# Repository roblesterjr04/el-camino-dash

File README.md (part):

# El Camino Dash

A modular, open hardware and firmware digital instrument cluster, built on a CAN bus and plug-in cards.

The reference build is the dash of a **1964 Chevrolet El Camino**: three round touch screens sit where the original
gauges were, a main board behind them is shaped to that dash, and a small console works like the car's radio. But
only the main board knows which car it is in. Everything else (the screens, the sensor card, the audio card, the
radio, GPS, the LTE gateway, the console) is a node on one CAN bus that plugs into a **standard 2×15 card slot** or a
4-pin cable port. **Draw a main board for your own car, boat, kit car or bench, give it the same slots, and every card
in this repository plugs straight in.** Design a new card, and it adds its readings, alerts and settings pages to
the dash without a line of change to the screen firmware.

> **Status: work in progress.** The display, console and audio firmware run on bench hardware (Waveshare ESP32-P4
> round display boards, ESP32 dev kits). Nothing is installed in the car yet. Several cards exist as KiCad designs and
> as simulators in [`tools/`](tools/) but have not been built. Each README states what has and has not been tested
> on hardware. See [Status](#status).
>
> **Updated often; issues are not monitored, pull requests are welcome.** See [Contributing](#contributing).

## Contents

- [A modular platform](#a-modular-platform)
- [What it does](#what-it-does)
- [System overview](#system-overview-the-el-camino-reference-build)
- [Hardware](#hardware)
- [Firmware](#firmware)
- [Repository layout](#repository-layout)
- [Getting started](#getting-started)
- [Firmware updates without USB](#firmware-updates-without-usb)
- [Tests](#tests)
- [Making the boards](#making-the-boards)
- [Documentation map](#documentation-map)
- [Status](#status)
- [History](#history)
- [Contributing](#contributing)
- [Safety](#safety)
- [License](#license)

## A modular platform

```
          your main board                              the cards (unchanged, from any project)
  ┌───────────────────────────────┐
  │ shaped for your dash          │      ┌────────┐ ┌────────┐ ┌────────┐ ┌────────┐ ┌────────┐
  │ 1–3 screen headers            │◄─────┤ sensor │ │ audio  │ │ radio  │ │  GPS   │ │ yours  │
  │ 1–6 card slots (2×15)         │ slot │ card   │ │ card   │ │ card   │ │ card   │ │        │
  │ power, fuses, WAKE            │      └────────┘ └────────┘ └────────┘ └────────┘ └────────┘
  │ CAN bus, terminated at ends   │
  │ cable ports ──► console       │      every card: CAN + power on the slot, node number from the slot,
  └───────────────────────────────┘      services found by discovery, no configuration
```

The platform is three agreements, each documented in full:

| Agreement | What it fixes | Document |
| --- | --- | --- |
| **The card slot** | A 2×15, 2.54 mm socket: power (5 V, 3.3 V, switched and constant 12 V, AUX 12 V), CAN, a slot-ID resistor, WAKE, dash-light and reverse levels, an I2S digital audio rail and an analog audio bus. 80 × 60 mm cards standing on edge | [`docs/hardware/main_board_guide.md`](docs/hardware/main_board_guide.md) (designing a main board), [`docs/hardware/accessory_ports.md`](docs/hardware/accessory_ports.md) (the slot spec) |
| **The CAN bus** | Classic CAN, 500 kbit/s, terminated only on the main board; node numbers from the slot (`0x14 + slot − 1`); IDs as `channel base + node` | [`docs/protocols/can_guide.md`](docs/protocols/can_guide.md) (the guide), [`docs/protocols/can_bus.md`](docs/protocols/can_bus.md) |
| **The channel protocol** | How a card announces itself and uses the dash: alerts, sensor readings, menu pages, input, sounds, discovery | [`docs/protocols/can_channels.md`](docs/protocols/can_channels.md) |

What that buys you:

- **A main board is cheap to redraw.** It has no microcontroller: just power, the bus, the slots, the screen headers
  and the vehicle connectors. [`BenchBoard/`](BenchBoard/) (100 × 100 mm, two slots, one screen) is a complete
  small example; [`DigiDash2/`](DigiDash2/) is the full El Camino board.
- **Cards need no configuration.** A card reads its slot from a resistor on the main board and takes its node number
  from it. Two identical cards never clash; moving a card just renumbers it.
- **The dash finds services by discovery.** Cards announce what they produce and consume; the screens find the audio
  sink, the GPS or the internet gateway from those announcements.
- **New cards extend the dash without firmware changes elsewhere.** A card that publishes a SENSOR reading gets it
  logged and shown; one that defines an ALERT gets a chime and a banner; one that describes UI items gets a page in
  the menu on the round screens and on the console.
- **Fewer screens or slots is fine.** One screen runs as the center; slots can be any subset of the six.
- **The sensor card is a card too.** If your car's senders, speed sensor or tach differ, change the sensor card
  (or calibrate it from the menu), not the main board.

Ideas for cards nobody has built yet: transmission or oil temperature, wideband O2, tire pressure, parking sensors
(PLAY a tick sound on the audio card), steering-wheel buttons (INPUT), a data logger, a voice assistant on the I2S rail.
`tools/cards_sim.py` already simulates several of them, so the dash side can be tried before the hardware exists.

## What it does

- **Gauges.** Speed, odometer and trip, tach, fuel, oil pressure, coolant temperature, battery voltage, charge lamp,
  efficiency. Vector faces (LVGL) scale to 720×720 and 800×800 panels. If sensor data stops for 400 ms the needles
  fall to rest and the face shows **NO DATA** rather than a false zero.
- **Themes.** Classic (black glass, chrome, cream numerals), Modern (flat, orange arcs) and Fallout (green phosphor).
  A long press on the center screen changes all three screens at once.
- **Sensors on CAN.** The sensor card reads the original senders, the speed sensor, the tach signal, ignition, battery
  and the alternator lamp, keeps the odometer in FRAM, and sends the readings on CAN. Calibration is done from the
  menu ([`docs/protocols/sensor_calibration.md`](docs/protocols/sensor_calibration.md)).
- **Audio and phone.** The audio card is a Bluetooth A2DP / AVRCP / HFP sink with two stereo DACs (front and rear), a
  microphone input, a 10-band equaliser, fader and balance. Now playing, album art and the call card appear on the
  screens; calls are answered from the console or the touch screen.
- **Radio head unit.** The console (ESP32-S3, 256×64 OLED, two RetroSound-style knobs, IR receiver) selects the
  source, tunes the radio, handles calls and pairing, and shows every card's settings page.
- **Accessory protocol.** Cards announce themselves and publish alerts, sensors, menu pages, input and sounds through a
  documented CAN channel protocol ([`docs/protocols/can_channels.md`](docs/protocols/can_channels.md)), so a new card
  can add a page to the menu without changing the screen firmware.
- **More.** GPS time and location with a POSIX time zone, a reversing camera on the center screen (TVP5150 decoder),
  per-screen touch menus, settings kept in NVS and on SD. The cluster never uses Wi-Fi, apart from the console's
  firmware-update hotspot, which you open by hand while the car is parked.
- **Firmware updates without USB.** New firmware for the screens and the console goes in from a phone or a laptop
  with every board still in the dash: see [Firmware updates without USB](#firmware-updates-without-usb).

## System overview: the El Camino reference build

```
                         ┌──────────────── DigiDash main board (behind the screens) ────────────────┐
  vehicle 12 V ─────────►│ power, ignition / WAKE, reverse and dash-light sense, video decoder     │
  senders, speed, tach ─►│                                                                          │
  camera ───────────────►│  [J5] LEFT screen        [J1] CENTER screen        [J4] RIGHT screen     │
                         │  speedometer             tach / clock / media /    fuel / oil / temp /   │
                         │  ESP32-P4, node 0x02     efficiency, camera, GPS   charge                │
                         │                          ESP32-P4, node 0x01       ESP32-P4, node 0x03   │
                         │                                                                          │
                         │  six card slots (2×15): CAN, 5 V, 3.3 V, AUX 12 V, slot ID, I2S rail     │
                         │   ├ Sensor card   (node 0x04)   senders, speed, tach, odometer (FRAM)    │
                         │   ├ Audio card    (node 0x14+)  Bluetooth, DACs, mic, EQ; I2S clock master│
                         │   ├ Radio card                  Si4735 AM/FM with RDS                    │
                         │   ├ GPS card                    remote GPS puck                          │
                         │   └ LTE card                    SIMCom A7670 gateway                     │
                         │                                                                          │
                         │  cable ports ── ConsoleBoardRS (node 0x13): OLED, 2 knobs, IR            │
                         │  USB-CAN tap                                                             │
                         └──────────────────────────── CAN 500 kbit/s ──────────────────────────────┘
```

- **One CAN bus** (500 kbit/s, 11-bit IDs, terminated at the left and right screens) links everything. The cluster's
  own traffic (sensor frames, theme, settings, media, phone, console) is in
  [`docs/protocols/can_bus.md`](docs/protocols/can_bus.md); the accessory channel protocol that cards use is in
  [`docs/protocols/can_channels.md`](docs/protocols/can_channels.md).
- **The three screens run one firmware image.** Each reads its position from a strap on the main board's header
  (left to GND, right to 3.3 V, center open) and becomes the speedometer, the center screen or the right screen.
- **The center screen** owns the cluster settings, GPS time and location, the time zone, the camera and SD storage,
  and re-sends theme and settings to the others. Any screen can host the touch menu.
- **The sensor card is the source of truth** for readings and the odometer. A serial fallback (the original UART fan-out)
  can still feed the screens directly through a jumper.
- **The I2S rail** is a five-line digital audio bus to every slot. The audio card is its clock master; the radio and
  other cards ask for its return line before they send audio.

Pinouts, connectors and power are in [`docs/hardware/accessory_ports.md`](docs/hardware/accessory_ports.md) and
[`WIRING_PINOUT.md`](WIRING_PINOUT.md).

## Hardware

Every board is a KiCad 10 project generated by Python scripts in its `generate/` folder. The full list, with revision
history and status, is in [`HARDWARE.md`](HARDWARE.md).

| Board | What it is |
| --- | --- |
| [`DigiDash2/`](DigiDash2/) | Main board, rev 2: three screen headers, six card slots, power, video decoder, 4 layers, SMD assembled by the fab |
| [`DigiDash3/`](DigiDash3/) | Main board, rev 3: rev 2 with every part through-hole, 2 layers, for hand assembly |
| [`DigiDash/`](DigiDash/) | Main board, rev 1 (superseded): plug-in dev boards and accessory headers |
| [`SensorCard/`](SensorCard/) | Sensor card rev A: ATmega2560 + MCP2515 |
| [`SensorCard2/`](SensorCard2/) | Sensor card rev B: STM32G0B1 with built-in FDCAN, 2 layers |
| [`AudioCarrier/`](AudioCarrier/) | Audio card: ESP32-DevKitC-VE in sockets, 2× PCM5102A DAC, PCM1808 ADC + mic preamp, RCA outputs |
| [`RadioCard/`](RadioCard/) | AM/FM radio card: Si4735 tuner, STM32G0B1 |
| [`GPSCard/`](GPSCard/), [`GPSCard2/`](GPSCard2/) | GPS card: STM32G0B1 (rev A, SMD) or PIC18F26Q83 (rev B, through-hole) |
| [`LTECard/`](LTECard/) | LTE gateway card: ESP32-S3 + SIMCom A7670 core board |
| [`AICard/`](AICard/) | AI voice card: ESP32-S3 front end + a Pi-header Linux compute module (speech, local and online models). Not ordered; the module's fit is provisional |
| [`ConsoleBoardRS/`](ConsoleBoardRS/) | Console: ESP32-S3, SSD1322 OLED, RetroSound knobs on RJ9, IR receiver |
| [`ConsoleBoard/`](ConsoleBoard/) | Console, earlier variant with keys and encoders on the board |
| [`BenchBoard/`](BenchBoard/) | Bench stand-in for the main board: two slots, one screen, a USB-CAN header |
| [`Panel/`](Panel/) | All current boards on one fab panel |
| [`Housing/`](Housing/) | Onshape FeatureScript for the cluster housing; a turn-signal indicator puck |

Off-the-shelf parts: the screens are **Waveshare ESP32-P4-WIFI6-Touch-LCD-4C** (4", 720×720) on the left and right and
**-3.4C** (3.4", 800×800) in the center; they plug into the main board on 2×20 headers.

## Firmware

PlatformIO projects under [`firmware/`](firmware/). Shared code is in libraries; every board runs the firmware that
ships (there are no separate bench builds). Details, gestures, console commands and panel targets:
[`firmware/README.md`](firmware/README.md).

| Directory | Runs on | What |
| --- | --- | --- |
| [`firmware/esp32_p4_display`](firmware/esp32_p4_display/) | All three screens (ESP32-P4) | One image; position from the strap |
| [`firmware/esp32_p4_ui`](firmware/esp32_p4_ui/) | library | LVGL screen layer, gauge faces, menu, media / phone / accessory pages, touch |
| [`firmware/esp32_p4_common`](firmware/esp32_p4_common/) | library | Sensor link, panel setup, cluster I2C, watchdog, boot splash |
| [`firmware/elc_can`](firmware/elc_can/) | library | CAN IDs, frame codecs, TWAI driver with heartbeat and bus-off recovery |
| [`firmware/esp32s3_console`](firmware/esp32s3_console/) | Console (ESP32-S3) | Radio head unit UI on the OLED |
| [`firmware/esp32_classic_bt_audio`](firmware/esp32_classic_bt_audio/) | Audio card (classic ESP32) | Audio sink and Bluetooth bridge; builds [`arduino/sketches/esp32_audio_bridge`](arduino/sketches/) |
| [`firmware/sensor_card`](firmware/sensor_card/) | Sensor card rev A (ATmega2560) | Senders, speed, tach, odometer, calibration |
| [`firmware/sensor_card_stm32`](firmware/sensor_card_stm32/) | Sensor card rev B (STM32G0B1) | Port of rev A; same logic, new hardware layer |
| [`firmware/ai_card`](firmware/ai_card/) | AI voice card (ESP32-S3) | CAN node, rail audio, wake word, compute-module power, the assistant's allow-list |
| [`firmware/ai_agent`](firmware/ai_agent/) | AI card's compute module (Linux) | Speech to text, intents, on-board and online models, speech |
| [`firmware/esp32_p4_display_litmus`](firmware/esp32_p4_display_litmus/) | Any P4 panel | Panel bring-up test |
| [`arduino/sketches/`](arduino/sketches/) | various | Rev 1 sensor pack (ATmega328P), the audio bridge source, older experiments |

The radio, GPS, LTE and other cards do not have firmware yet; their behaviour on CAN is simulated by
[`tools/can_relay.py`](tools/can_relay.py) and the `*_sim.py` modules next to it.

## Repository layout

```
el-camino-dash/
├── README.md               this file
├── HARDWARE.md             every board: lineage, status, how to regenerate and order
├── WIRING_PINOUT.md        vehicle harness and screen header pinouts
├── firmware/               PlatformIO firmware and shared libraries
├── arduino/                Arduino sketches and arduino-cli helpers (rev 1 sensor pack, audio bridge source)
├── docs/
│   ├── protocols/          wire formats: CAN bus, CAN channels, sensor UART, USB link, calibration, I2C
│   └── hardware/           specs and plans: accessory ports, cards, housing envelope, harnesses, costing
├── tools/                  bench relay and card simulators, gauge / console previews, fab export scripts
├── scripts/                asset export (boot splash to RGB565)
├── assets/                 boot splash and the original Classic gauge art (design reference)
├── <Board>/                one directory per KiCad board (see Hardware)
└── Housing/                enclosure CAD
```

Each directory has its own README.

## Getting started

### Prerequisites

- **Python 3** for the tools and generators.
- **PlatformIO 6.1.18 or later.** Each `flash.sh` installs it into a local `.venv`; for a PlatformIO you installed
  yourself, add the builder's Python packages with `firmware/requirements-pio.txt` (see
  [`firmware/boards/README.md`](firmware/boards/README.md)). Platform and library versions are pinned in each `platformio.ini`.
- **A C++17 compiler** (Apple clang or gcc) for the host tests and the previews.
- **KiCad 10** to open or regenerate the boards.

### See the gauges without hardware

The faces render on a desktop with the same code that runs on the screens:

```bash
cd firmware/esp32_p4_display && pio run -e display-waveshare3c4 && cd -   # once, to fetch LVGL
tools/gauge_preview/build.sh
python3 tools/gauge_preview/preview.py faces.png 0,1,0 2,1,0 1,1,0
```

The console's OLED has the same kind of preview in [`tools/console_preview/`](tools/console_preview/). See
[`tools/README.md`](tools/README.md).

### Flash a screen

Any Waveshare ESP32-P4 round display board will do. Pick the environment that matches the panel
(`display-waveshare3c4` = 3.4" 800×800, `display-waveshare4c` = 4" 720×720); never flash one panel's profile on the
other.

```bash
cd firmware/esp32_p4_display
./flash.sh -e display-waveshare3c4 --upload-port /dev/cu.usbmodem…
```

Off the main board the position strap is open, so the board starts as the center screen. Type `role left`,
`role right` or `role auto` on its serial console (115200) to change that.

### Run a bench without a main board

[`tools/can_relay.py`](tools/can_relay.py) connects every board plugged into the computer over USB as if they were
on one CAN bus ([`docs/protocols/usb_link.md`](docs/protocols/usb_link.md)). It also sends a simulated drive in place
of the sensor card, the computer's clock in place of GPS, and simulated radio, audio, GPS, LTE and other cards:

```bash
python3 tools/can_relay.py            # every USB serial port found
python3 tools/can_relay.py --frames   # also log the frames
```

With a real CAN bus, plug a USB-CAN adapter into the main board's tap or the [`BenchBoard`](BenchBoard/).

### Other boards

```bash
firmware/esp32s3_console/flash.sh --upload-port /dev/cu.usbmodem…         # console
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
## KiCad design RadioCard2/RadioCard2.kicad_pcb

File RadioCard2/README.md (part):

# Radio card, rev B (through-hole)

The hand-assembled version of the [radio card](../RadioCard/README.md). Same job, same **80 × 60 mm slot card**, same
slot use (CAN, the I2S rail's BCK / WS in and RET out) and CAN IDs (`docs/hardware/radio_card.md`). The difference is
that **every part is through-hole**, so you can solder the whole board yourself, and the tuner is a plug-in module:

- the owner's **Si4737-C40-GU breakout** (FMBreakout.brd, OSH Park, 22.4 × 29.4 mm) in a **1×8 and a 1×9 socket**
  (J6 / J7), in place of rev A's Si4735-D60 (a DigiKey-only SSOP that had to be machine-placed). The Si4737 is AM / FM /
  weather band + RDS with digital audio out; it has no SW / LW, which this card never used
- a **PIC18F26Q83-I/SP** (SPDIP-28, in a socket), as [GPSCard2](../GPSCard2/README.md): PIC18 at 64 MHz with its own
  **CAN FD controller** (run as classic CAN at 500 kbit/s), I2C and 5 UARTs, with a 16 MHz HC-49 crystal (4x PLL)
- an **MCP2562-E/P** CAN transceiver (DIP-8; VDD 5 V, VIO 3.3 V, STBY low, no termination)
- a **74HC125** (DIP-14) as the RET buffer, off at reset, and an **MCP1700-3302E/TO** 3.3 V regulator (TO-92)
- the **edge-mount SMA** of rev A (Amphenol 132289, already on hand; the one part soldered by hand on both faces of the
  board edge) and the AM loopstick header J5 on the top edge
- **J3, a 6-pin Microchip ICSP header** and **J4** debug serial, both right angle on the left edge; two 3 mm LEDs
- axial 1/4 W resistors (10.16 mm pitch), radial capacitors (2.54 mm), an axial ferrite bead and an axial 56 nH inductor

**Antenna ESD: D2 is not fitted, D4 / D5 and SG1 stand in for it.** The TPD1E0B04 (0.13 pF) has no through-hole version,
and nothing through-hole comes close to AN383's ≤ 1 pF. In its place: **SG1**, a 0.25 mm PCB spark gap (bare copper, nothing
to fit) right under the SMA's centre pin, which takes the bulk of a big static hit, and **D4 / D5**, two 1N5711 Schottky
diodes back to back from the antenna node to ground, which clamp what gets past it to about ±0.4 V (the tuner input's
limit). The cost is about 4 pF on the antenna node: some FM signal, and L1 has to be tuned with them in (see
[Tuning L1](#tuning-l1)). If reception suffers, compare with them lifted. D2's 0402 pads stay on the board.

| Files | |
| --- | --- |
| `RadioCard2.kicad_sch` / `.kicad_pcb` / `.kicad_pro` | The card: 80 × 60 mm, 2 layers, every part on the parts side (F). KiCad 10 |
| `RadioCard2_BOM.csv` | Parts list (hand assembly) |
| `fab/` | Gerbers and drill files (`RadioCard2_gerbers.zip`) for a bare-board order. Nothing is machine-placed: the placement files list only J2, the edge-mount SMA, which you solder yourself |
| `generate/` | Scripts that produced the files: `gen_sch.py` new (rev A's circuit on GPSCard2's parts), `gen_pcb.py` from `GPSCard2/generate/` with rev A's RF keep-out. Stock KiCad symbols and footprints only |

## Signal paths

```
Slot BCK (15) ── R8 2k ── J6 pin 3  P3 = GPO3 / DCLK       (also the tuner's reference clock: RCLKSEL = DCLK)
Slot WS  (16) ── R7 2k ── J6 pin 2  DFS                    (C10 2.2 pF to GND on the WS side; R9 / R10 100k idle pull-downs)
J6 pin 1 DOUT ── R6 604 ── U5 74HC125 buffer A (OE = RA4, 10k up = off) ── R15 33 ── Slot RET (18)
Slot MCLK (24) ── R12 0 R (NOT FITTED) ── J7 pin 4 RCLK (R13 100k to GND)
SMA J2 ── SG1 gap to GND ── D4 / D5 1N5711 pair to GND ── L1 56 nH to GND ── C12 1 nF C0G ── J6 pin 6 FMI      J6 pin 7 RFG = GND
J5 (loopstick) ── C13 470 nF ── J6 pin 8 AMI                       JP2 (no shunt) joins the SMA node to the AM node
+3V3 ── FB1 ── +3V3A ── J7 pin 3 (3.3V, VA and VD on the breakout), C3 10 uF + C4 100 nF at the pin
PIC RC3 / RC4 (SCL1 / SDA1) ── J7 pins 6 / 5 SCLK / SDIO   (pull-ups: the breakout's own 10k to its 3.3 V)
PIC RA2 ── J7 pin 8 RST (R11 100k to GND)    PIC RB0 ── J6 pin 4 P2 = GPO2 / INT    JP1 ── J7 pin 7 SEN
Slot CANH / CANL (5 / 6) ── U2 MCP2562 ── TXD ◄ RB2 CANTX by PPS (pin 23),  RXD ── R5 1k ──► RB3 CANRX (pin 24)
Slot ID (11): R1 10k to 3.3 V here, the slot's resistor to GND on the main board ──► RA1 ANA1 (pin 3)
Slot +5 V (1 / 2) ── U3 MCP1700-3.3 ── +3V3 (PIC, MCP2562 VIO, 74HC125, FB1)
```

### The breakout's pins (J6 / J7)

As the breakout's own silk names them, each header counted from the **headphone-jack end** (socket pin 1). The breakout
sits **upside down** on the card: jack end toward the slot (silk "jack end"), so its FMI / AMI pins are nearest the SMA.

| Socket pin | J6 (breakout left header) | Si4737 pin | J7 (breakout right header) | Si4737 pin |
| --- | --- | --- | --- | --- |
| 1 | DOUT | 1 | LOUT (open) | 24 |
| 2 | DFS | 2 | ROUT (open) | 23 |
| 3 | P3 = GPO3 / DCLK | 3 | 3.3V (VA + VD) | 20, 21 |
| 4 | P2 = GPO2 / INT | 4 | RCLK | 19 |
| 5 | P1 = GPO1 (open: high or open at reset) | 5 | SDIO | 18 |
| 6 | FMI | 8 | SCLK | 17 |
| 7 | RFG (RF ground) | 9 | SEN | 16 |
| 8 | AMI | 12 | RST | 15 |
| 9 | | | GND | 13, 14 |

On the breakout itself: the DBYP capacitor (pin 22), 10k pull-ups on SDIO / SCLK and the headphone jack on LOUT / ROUT.
It has **no crystal** (the reference comes from DCLK), **no supply decoupling** (C3 / C4 here) and **no antenna coupling
capacitors** (C12 / C13 here).

### MCU pins (PIC18F26Q83, SPDIP-28)

| Pin | Port | Function | To |
| --- | --- | --- | --- |
| 1 | RE3 | MCLR / VPP | J3 pin 1, R2 10k to 3.3 V |
| 3 | RA1 | ANA1 | slot ID |
| 4 | RA2 | GPIO out | tuner RST (R11 100k to GND holds it in reset until the firmware runs) |
| 6 | RA4 | GPIO out | RET buffer OE, active low (R14 10k up = buffer off at reset and on a blank chip) |
| 8, 19 | VSS | GND | |
| 9 / 10 | RA7 / RA6 | OSC1 / OSC2 | Y1 16 MHz, C6 / C7 27 pF |
| 12 | RC1 | GPIO | LED D1 TUNED (high = on, R3 1k) |
| 13 | RC2 | GPIO | LED D3 STEREO / RDS (high = on, R4 1k) |
| 14 | RC3 | SCL1 | tuner SCLK |
| 15 | RC4 | SDA1 | tuner SDIO |
| 20 | VDD | 3.3 V | C5 100 nF |
| 21 | RB0 | INT0 | tuner GPO2 / INT |
| 23 | RB2 | CANTX (PPS) | MCP2562 TXD |
| 24 | RB3 | CANRX (POR default) | MCP2562 RXD (through R5 1k) |
| 25 | RB4 | U2TX (PPS) | J4 pin 2 |
| 26 | RB5 | U2RX (PPS) | J4 pin 3 |
| 27 | RB6 | ICSPCLK | J3 pin 5 |
| 28 | RB7 | ICSPDAT | J3 pin 4 |

All other pins are open: set them to outputs driven low, or analog, in firmware.

| Connector | Pins |
| --- | --- |
| J1, slot (2×15, right angle, bottom edge) | As rev A. Used: 1 / 2 +5 V, 3 / 4 / 7 / 19 / 20 GND, 5 CANH, 6 CANL, 11 slot ID, 15 BCK, 16 WS, 18 RET, 24 MCLK (only through R12, not fitted) |
| J2, antenna (SMA, edge mount, top edge) | Centre = FM antenna node, legs = GND (both faces) |
| J3, ICSP (1×6, right angle, left edge) | 1 MCLR/VPP, 2 VDD (3.3 V), 3 GND, 4 ICSPDAT, 5 ICSPCLK, 6 not used. Pin 1 is the lowest pin (PICkit / Snap pinout) |
| J4, debug serial (1×3, right angle, left edge) | 1 GND, 2 TX (out of the card), 3 RX (into the card); UART2, 3.3 V. Pin 1 is the lowest pin |
| J5, AM loopstick (1×2, right angle, top edge) | 1 AM node, 2 GND |
| J6 / J7, tuner breakout (1×8 / 1×9 female, 17.78 mm apart) | See the table above |
| JP1, tuner address (1×3 + shunt) | 1-2 = SEN low = I2C 0x11 (the firmware default); 2-3 = 0x63 |
| JP2, AM from whip (1×2, no shunt) | A shunt feeds the SMA to the AM input too (needs a car-whip AM network that AN383 does not give) |

## Board

- **Outline:** 80 × 60 mm, no mounting holes, the slot and the case hold it (as rev A).
- **J1** is placed exactly as on rev A and GPSCard2. **U1** lies along the board in the middle-left with Y1 under it,
  ICSP and debug on the left edge, as GPSCard2. **The breakout** sits at the top right (x 52-74, y 9-39) on its two
  sockets, jack end toward the slot: FMI / AMI at its top, near **J2** (SMA, x 70) and **J5** (x 58); DOUT / DFS / DCLK
  at its bottom, toward **U5** and the rail pins. **U2** sits above the slot's CAN pins, **U3** beside its 5 V pins.
- **RF keep-out:** no tracks on B in the top-right corner (x 60-80, y 0-23: the SMA, L1, the coupling caps and the
  breakout's RF pins), so the B ground pour is solid under the front end (as rev A).
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
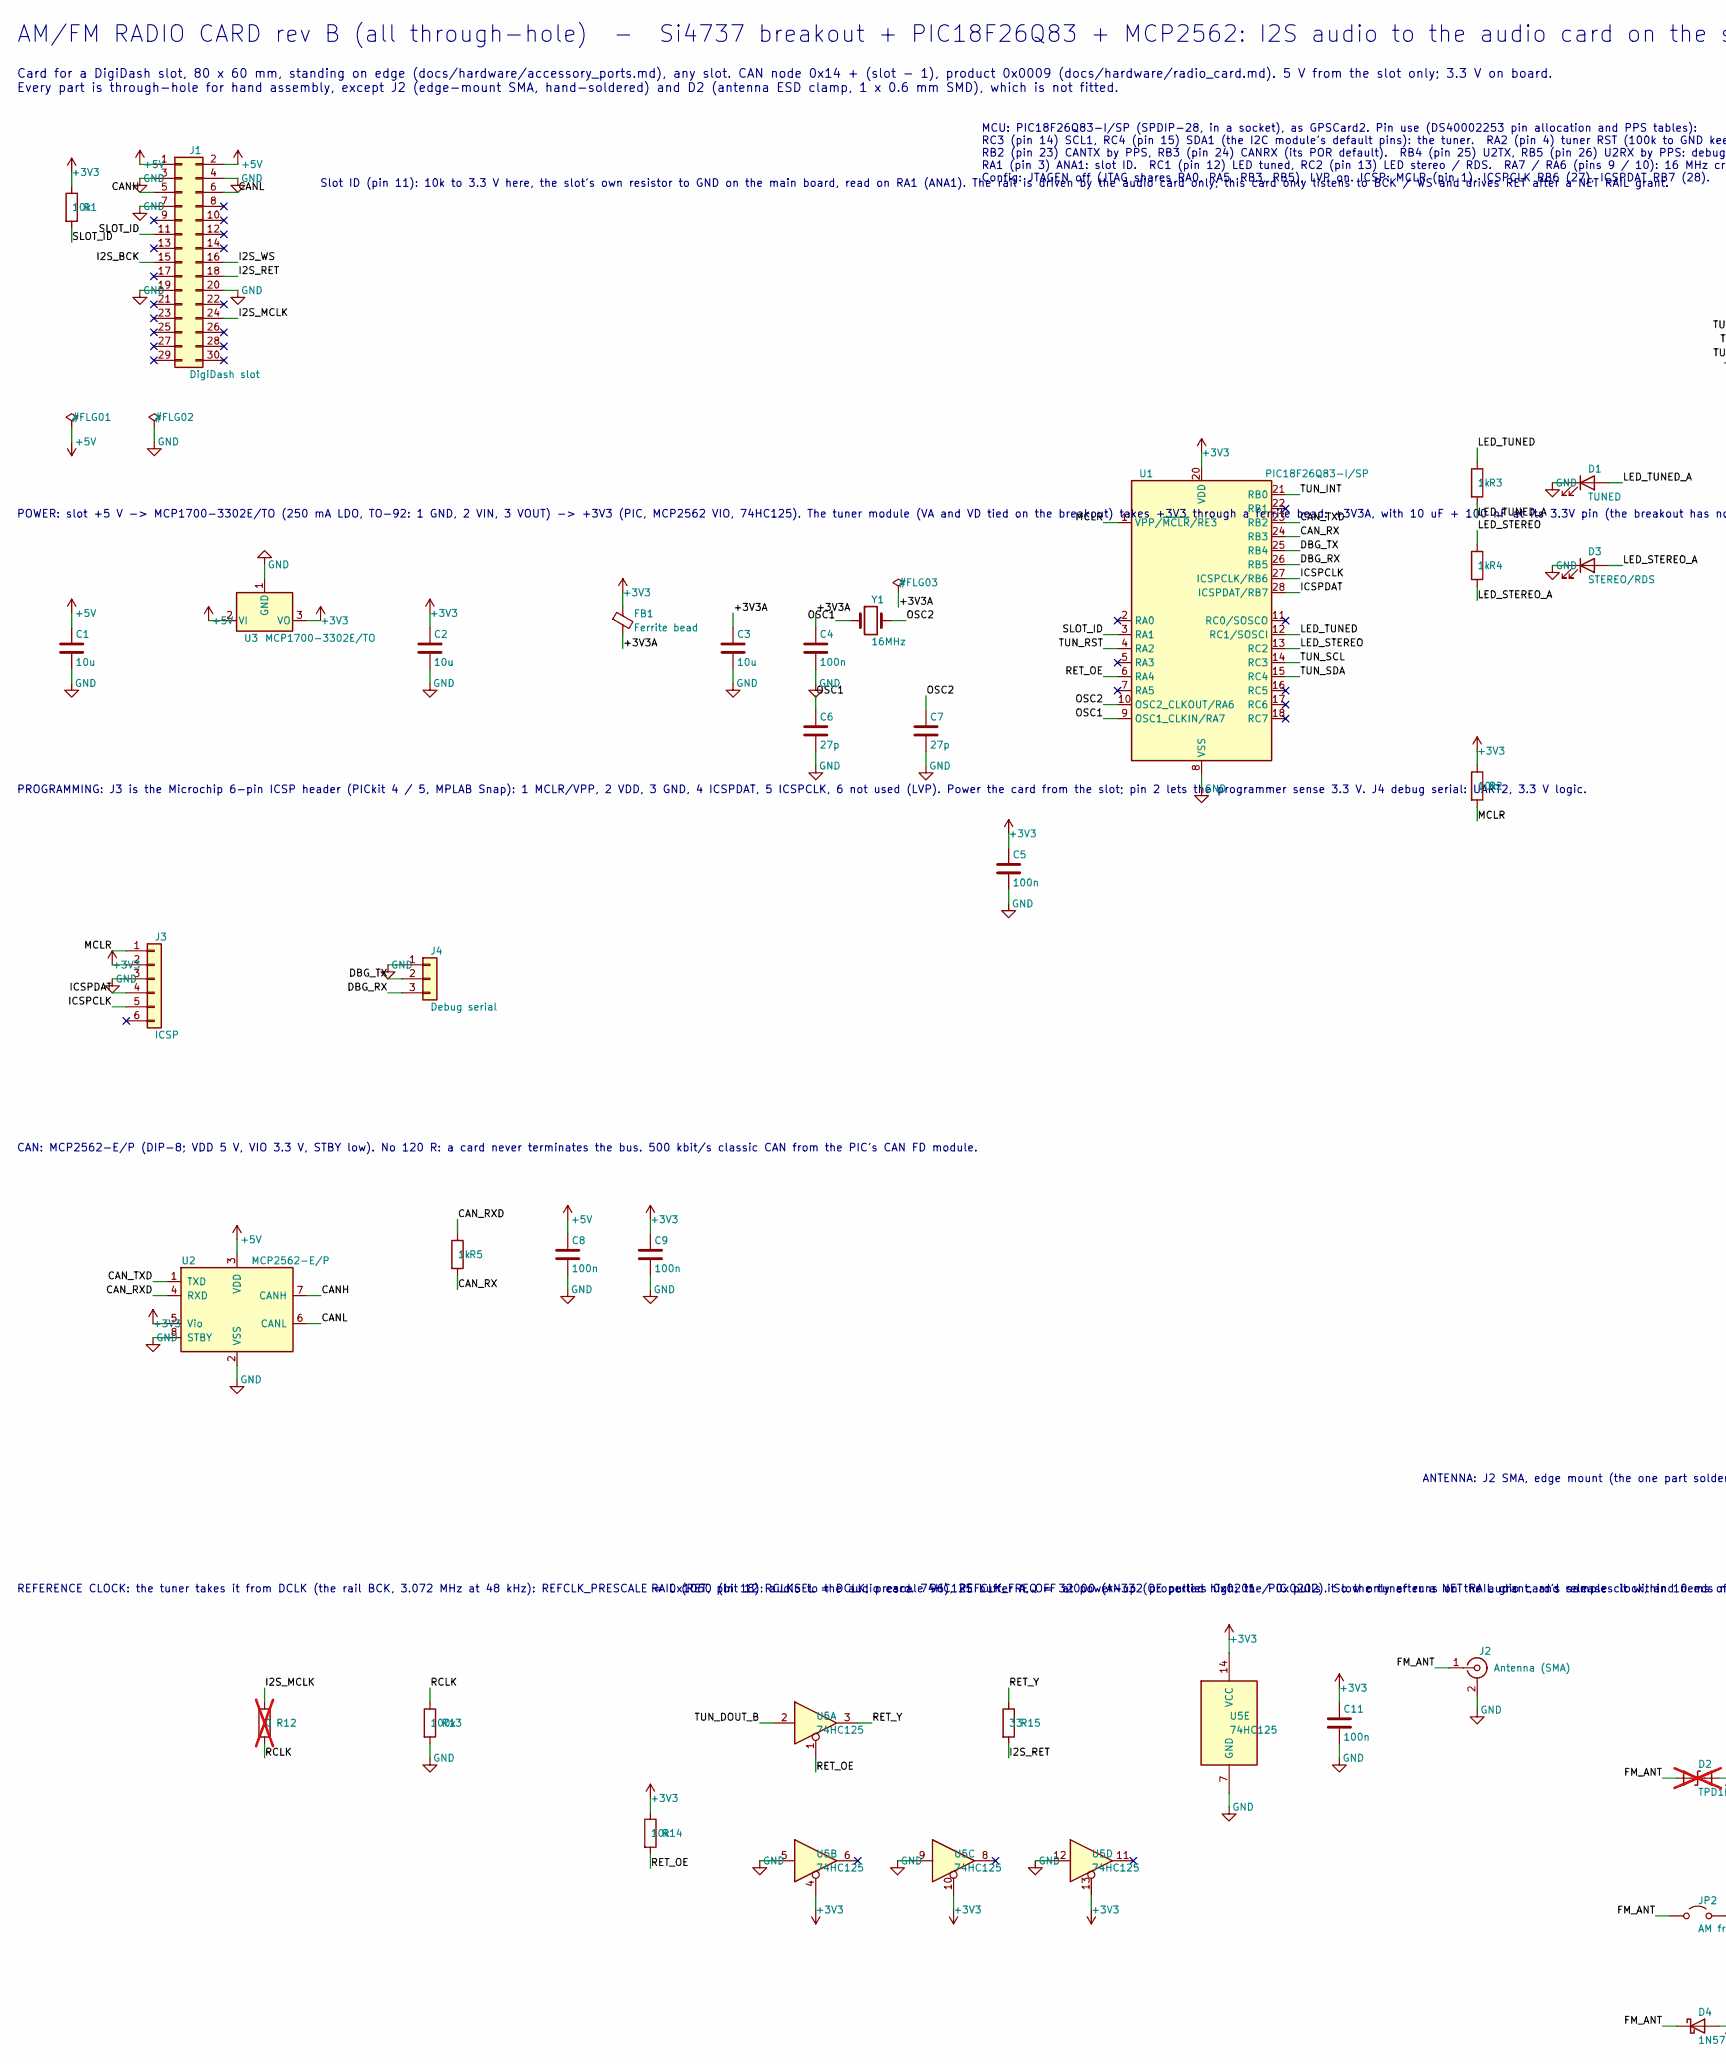
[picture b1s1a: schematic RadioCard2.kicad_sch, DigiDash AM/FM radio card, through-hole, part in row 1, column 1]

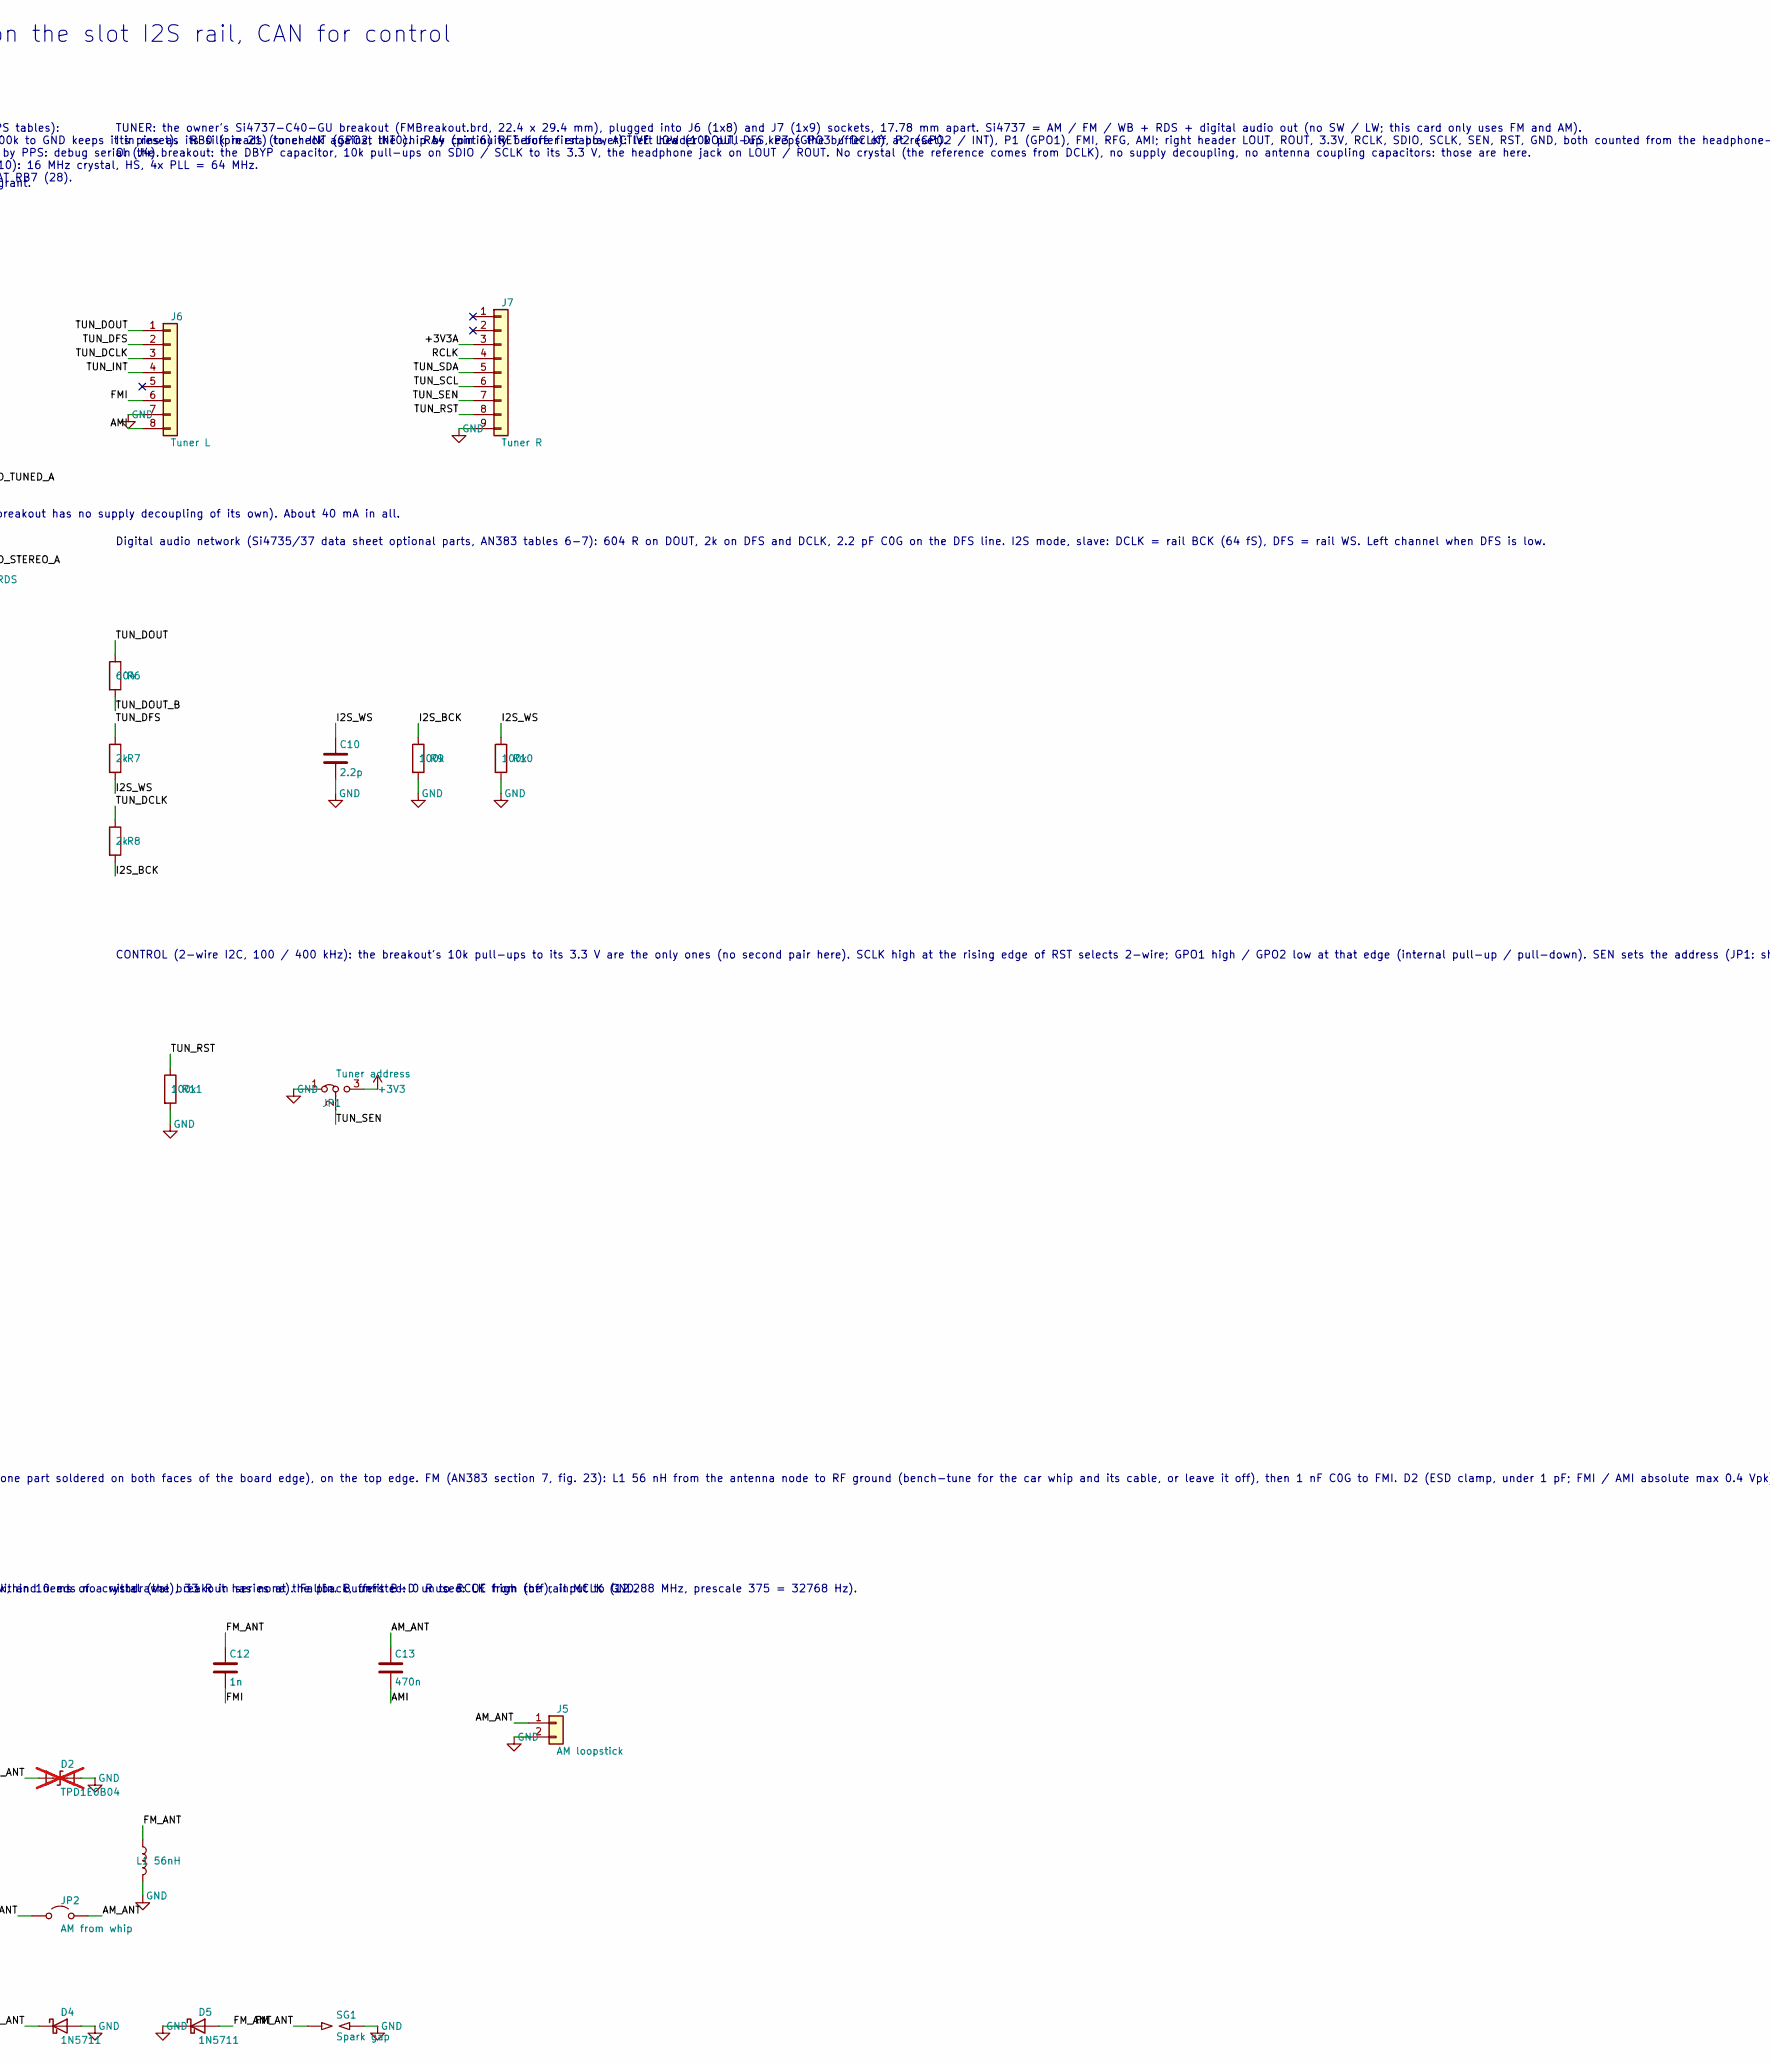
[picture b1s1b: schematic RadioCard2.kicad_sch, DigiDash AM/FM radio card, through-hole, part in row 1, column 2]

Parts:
C1, C2, C3: 10u; C_Disc_D5.0mm_W2.5mm_P2.50mm
C4, C5, C8, C9, C11: 100n; C_Disc_D5.0mm_W2.5mm_P2.50mm
C6, C7: 27p; C_Disc_D5.0mm_W2.5mm_P2.50mm
C10: 2.2p; C_Disc_D5.0mm_W2.5mm_P2.50mm
C12: 1n; C_Disc_D5.0mm_W2.5mm_P2.50mm
C13: 470n; C_Disc_D5.0mm_W2.5mm_P2.50mm
D1: TUNED; LED_D3.0mm
D2: TPD1E0B04; D_0402_1005Metric; not fitted
D3: STEREO/RDS; LED_D3.0mm
D4, D5: 1N5711; D_DO-35_SOD27_P2.54mm_Vertical_CathodeUp
FB1: Ferrite bead; L_Axial_L5.0mm_D3.6mm_P10.00mm_Horizontal_Murata_BL01RN1A2A2
J1: DigiDash slot; PinHeader_2x15_P2.54mm_Horizontal
J2: Antenna (SMA); SMA_Amphenol_132289_EdgeMount
J3: ICSP; PinHeader_1x06_P2.54mm_Horizontal
J4: Debug serial; PinHeader_1x03_P2.54mm_Horizontal
J5: AM loopstick; PinHeader_1x02_P2.54mm_Horizontal
J6: Tuner L; PinSocket_1x08_P2.54mm_Vertical
J7: Tuner R; PinSocket_1x09_P2.54mm_Vertical
JP1: Tuner address; PinHeader_1x03_P2.54mm_Vertical
JP2: AM from whip; PinHeader_1x02_P2.54mm_Vertical
L1: 56nH; L_Axial_L5.3mm_D2.2mm_P7.62mm_Horizontal_Vishay_IM-1
R1, R2, R14: 10k; R_Axial_DIN0207_L6.3mm_D2.5mm_P10.16mm_Horizontal
R3, R4, R5: 1k; R_Axial_DIN0207_L6.3mm_D2.5mm_P10.16mm_Horizontal
R6: 604; R_Axial_DIN0207_L6.3mm_D2.5mm_P10.16mm_Horizontal
R7, R8: 2k; R_Axial_DIN0207_L6.3mm_D2.5mm_P10.16mm_Horizontal
R9, R10, R11, R13: 100k; R_Axial_DIN0207_L6.3mm_D2.5mm_P10.16mm_Horizontal
R12: 0; R_Axial_DIN0207_L6.3mm_D2.5mm_P10.16mm_Horizontal; not fitted
R15: 33; R_Axial_DIN0207_L6.3mm_D2.5mm_P10.16mm_Horizontal
SG1: Spark gap; SparkGap_0.25mm
U1: PIC18F26Q83-I/SP; DIP-28_W7.62mm_Socket
U2: MCP2562-E/P; DIP-8_W7.62mm
U3: MCP1700-3302E/TO; TO-92_Inline_Wide
U5: 74HC125; DIP-14_W7.62mm
Y1: 16MHz; Crystal_HC49-4H_Vertical

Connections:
+3V3: C2.1, C5.1, C9.1, C11.1, FB1.1, J3.2, JP1.3 (B), R1.1, R2.1, R14.1, U1.20 (VDD), U2.5 (Vio), U3.3 (VO), U5.4, U5.10, U5.13, U5.14 (VCC)
+5V: C1.1, C8.1, J1.1, J1.2, U2.3 (VDD), U3.2 (VI)
/+3V3A: C3.1, C4.1, FB1.2, J7.3
/AMI: C13.2, J6.8
/AM_ANT: C13.1, J5.1, JP2.2 (B)
/CANH: J1.5, U2.7 (CANH)
/CANL: J1.6, U2.6 (CANL)
/CAN_RX: R5.2, U1.24 (RB3)
/CAN_RXD: R5.1, U2.4 (RXD)
/CAN_TXD: U1.23 (RB2), U2.1 (TXD)
/DBG_RX: J4.3, U1.26 (RB5)
/DBG_TX: J4.2, U1.25 (RB4)
/FMI: C12.2, J6.6
/FM_ANT: C12.1, D2.1 (A1), D4.1 (K), D5.2 (A), J2.1 (In), JP2.1 (A), L1.1, SG1.1
/I2S_BCK: J1.15, R8.2, R9.1
/I2S_MCLK: J1.24, R12.1
/I2S_RET: J1.18, R15.2
/I2S_WS: C10.1, J1.16, R7.2, R10.1
/ICSPCLK: J3.5, U1.27 (ICSPCLK/RB6)
/ICSPDAT: J3.4, U1.28 (ICSPDAT/RB7)
/LED_STEREO: R4.1, U1.13 (RC2)
/LED_STEREO_A: D3.2 (A), R4.2
/LED_TUNED: R3.1, U1.12 (RC1/SOSCI)
/LED_TUNED_A: D1.2 (A), R3.2
/MCLR: J3.1, R2.2, U1.1 (VPP/~MCLR/RE3)
/OSC1: C6.1, U1.9 (OSC1_CLKIN/RA7), Y1.1
/OSC2: C7.1, U1.10 (OSC2_CLKOUT/RA6), Y1.2
/RCLK: J7.4, R12.2, R13.1
/RET_OE: R14.2, U1.6 (RA4), U5.1
/RET_Y: R15.1, U5.3
/SLOT_ID: J1.11, R1.2, U1.3 (RA1)
/TUN_DCLK: J6.3, R8.1
/TUN_DFS: J6.2, R7.1
/TUN_DOUT: J6.1, R6.1
/TUN_DOUT_B: R6.2, U5.2
/TUN_INT: J6.4, U1.21 (RB0)
/TUN_RST: J7.8, R11.1, U1.4 (RA2)
/TUN_SCL: J7.6, U1.14 (RC3)
/TUN_SDA: J7.5, U1.15 (RC4)
/TUN_SEN: J7.7, JP1.2 (C)
GND: C1.2, C2.2, C3.2, C4.2, C5.2, C6.2, C7.2, C8.2, C9.2, C10.2, C11.2, D1.1 (K), D2.2 (A2), D3.1 (K), D4.2 (A), D5.1 (K), J1.3, J1.4, J1.7, J1.19, J1.20, J2.2 (Ext), J3.3, J4.1, J5.2, J6.7, J7.9, JP1.1 (A), L1.2, R9.2, R10.2, R11.2, R13.2, SG1.2, U1.8 (VSS), U1.19 (VSS), U2.2 (VSS), U2.8 (STBY), U3.1 (GND), U5.5, U5.7 (GND), U5.9, U5.12

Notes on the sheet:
AM/FM RADIO CARD rev B (all through-hole) - Si4737 breakout + PIC18F26Q83 + MCP2562: I2S audio to the audio card on the slot I2S rail, CAN for control
Card for a DigiDash slot, 80 x 60 mm, standing on edge (docs/hardware/accessory_ports.md), any slot. CAN node 0x14 + (slot - 1), product 0x0009 (docs/hardware/radio_card.md). 5 V from the slot only; 3.3 V on board. Every part is through-hole for hand assembly, except J2 (edge-mount SMA, hand-solder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
Slot ID (pin 11): 10k to 3.3 V here, the slot's own resistor to GND on the main board, read on RA1 (ANA1). The rail is driven by the audio card only; this card only listens to BCK / WS and drives RET after a NET RAIL grant.
POWER: slot +5 V -> MCP1700-3302E/TO (250 mA LDO, TO-92: 1 GND, 2 VIN, 3 VOUT) -> +3V3 (PIC, MCP2562 VIO, 74HC125). The tuner module (VA and VD tied on the breakout) takes +3V3 through a ferrite bead: +3V3A, with 10 uF + 100 nF at its 3.3V pin (the breakout has no supply decoupling of its own). Abo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
MCU: PIC18F26Q83-I/SP (SPDIP-28, in a socket), as GPSCard2. Pin use (DS40002253 pin allocation and PPS tables): RC3 (pin 14) SCL1, RC4 (pin 15) SDA1 (the I2C module's default pins): the tuner. RA2 (pin 4) tuner RST (100k to GND keeps it in reset). RB0 (pin 21) tuner INT (GPO2, INT0). RA4 (pin 6) RE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
PROGRAMMING: J3 is the Microchip 6-pin ICSP header (PICkit 4 / 5, MPLAB Snap): 1 MCLR/VPP, 2 VDD, 3 GND, 4 ICSPDAT, 5 ICSPCLK, 6 not used (LVP). Power the card from the slot; pin 2 lets the programmer sense 3.3 V. J4 debug serial: UART2, 3.3 V logic.
CAN: MCP2562-E/P (DIP-8; VDD 5 V, VIO 3.3 V, STBY low). No 120 R: a card never terminates the bus. 500 kbit/s classic CAN from the PIC's CAN FD module.
TUNER: the owner's Si4737-C40-GU breakout (FMBreakout.brd, 22.4 x 29.4 mm), plugged into J6 (1x8) and J7 (1x9) sockets, 17.78 mm apart. Si4737 = AM / FM / WB + RDS + digital audio out (no SW / LW; this card only uses FM and AM). Its pins as its silk reads (to check against the chip by continuity be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
Digital audio network (Si4735/37 data sheet optional parts, AN383 tables 6-7): 604 R on DOUT, 2k on DFS and DCLK, 2.2 pF C0G on the DFS line. I2S mode, slave: DCLK = rail BCK (64 fS), DFS = rail WS. Left channel when DFS is low.
CONTROL (2-wire I2C, 100 / 400 kHz): the breakout's 10k pull-ups to its 3.3 V are the only ones (no second pair here). SCLK high at the rising edge of RST selects 2-wire; GPO1 high / GPO2 low at that edge (internal pull-up / pull-down). SEN sets the address (JP1: shunt 1-2 = SEN low = 0x11; 2-3 = 0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
REFERENCE CLOCK: the tuner takes it from DCLK (the rail BCK, 3.072 MHz at 48 kHz): REFCLK_PRESCALE = 0x1060 (bit 12 RCLKSEL = DCLK, prescale 96), REFCLK_FREQ = 32000 (AN332 properties 0x0201 / 0x0202). So the tuner runs on the audio card's sample clock, and needs no crystal (the breakout has none).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
RAIL (RET, pin 18): audio to the audio card. 74HC125 buffer A, OFF at power-up (OE pulled high; the PIC pulls it low only after a NET RAIL grant, and releases it within 10 ms of a withdrawal), 33 R in series at the pin. Buffers B-D unused: OE high (off), input to GND.
ANTENNA: J2 SMA, edge mount (the one part soldered on both faces of the board edge), on the top edge. FM (AN383 section 7, fig. 23): L1 56 nH from the antenna node to RF ground (bench-tune for the car whip and its cable, or leave it off), then 1 nF C0G to FMI. D2 (ESD clamp, under 1 pF; FMI / AMI a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

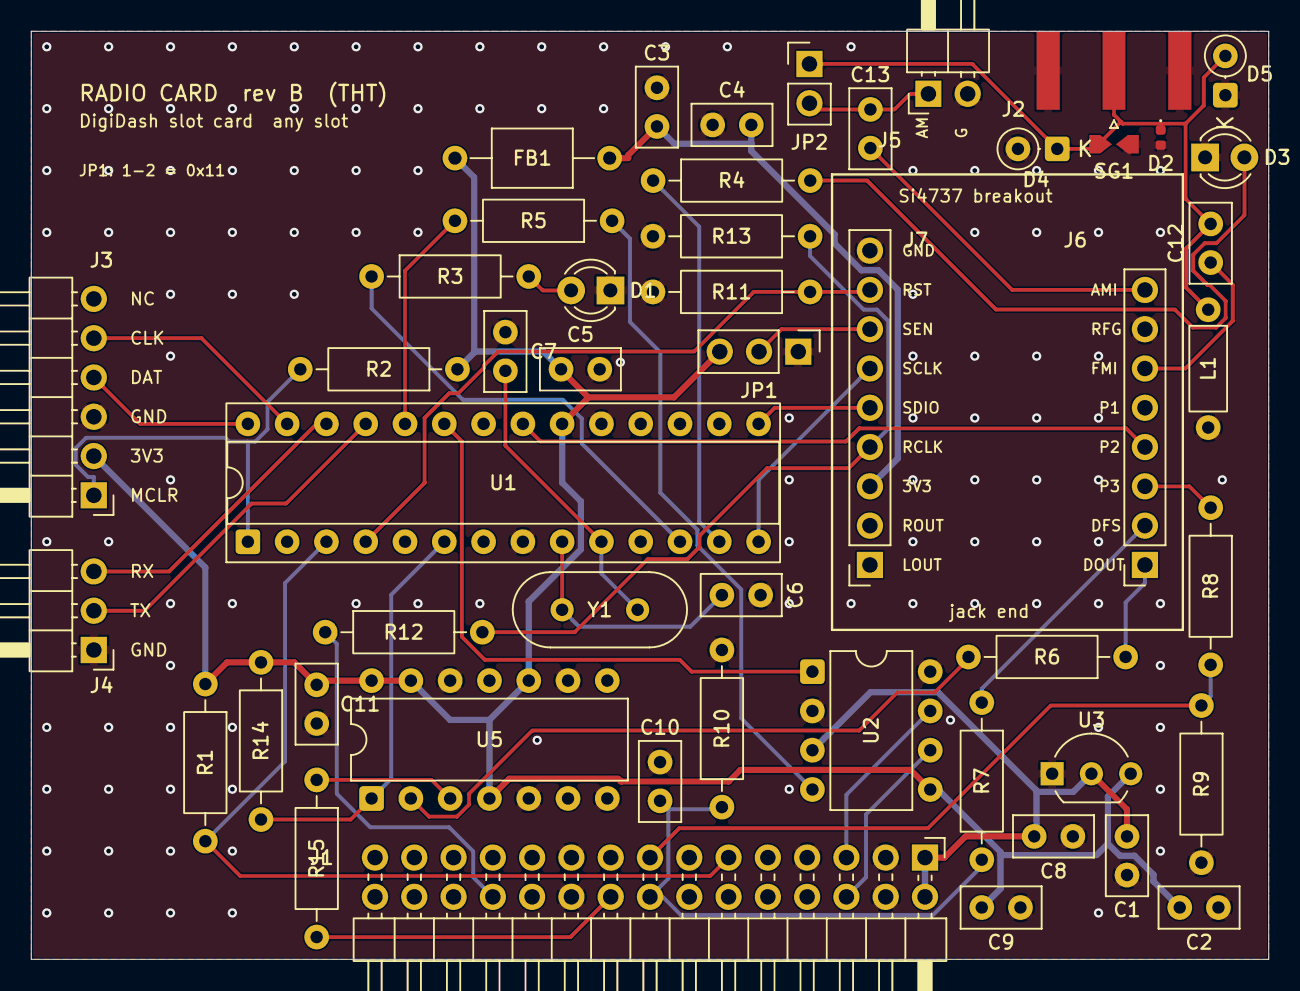
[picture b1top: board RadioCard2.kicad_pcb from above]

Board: 2 copper layers, 80.0 x 60.0 mm, 50 parts (0 on the bottom side), 41 nets.

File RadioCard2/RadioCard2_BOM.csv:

Qty,Designators,Manufacturer part,Description,Package,Type,Side,Notes
1,U1,Microchip PIC18F26Q83-I/SP,"MCU: PIC18, 64 MHz, 64 KB flash, 4 KB RAM, CAN FD, I2C, 5 UARTs, 1.8-5.5 V",SPDIP-28 (0.3 in),THT,Top,"Fit in a socket (next line). Notch / pin 1 toward J3 (left). Arrives blank: programmed over J3 (ICSP)"
1,U1 socket,"Any 28-pin 0.3 in (narrow) DIP socket","IC socket for U1",DIP-28 0.3 in,THT,Top,"Turned-pin or leaf type. Solder the socket, not the PIC"
1,U2,Microchip MCP2562-E/P,"CAN FD transceiver, VDD 5 V, VIO 3.3 V",PDIP-8,THT,Top,"An 8-pin 0.3 in socket fits too"
1,U3,Microchip MCP1700-3302E/TO,"LDO 3.3 V 250 mA (1 GND, 2 VIN, 3 VOUT)",TO-92,THT,Top,"Wide-spaced pads (2.54 mm): bend the outer legs out. Flat face as the silk shows"
1,U5,Texas Instruments SN74HC125N,"74HC125: quad 3-state buffer, OE active low (buffer A drives the rail's RET pin)",PDIP-14,THT,Top,"Runs at 3.3 V. Any 74HC125 / 74AHC125 in DIP-14. A 14-pin socket fits too"
1,Tuner,"Si4737-C40-GU breakout (FMBreakout.brd, OSH Park, owner-built)","AM / FM / WB + RDS tuner with digital audio out, on a 22.4 x 29.4 mm board with a 1 x 8 and a 1 x 9 male header",Module,Module,Top,"Already built. Plugs into J6 / J7, headphone jack toward the slot (silk 'jack end'). Check its header pinout against the chip by continuity before first power"
1,Y1,Abracon ABL-16.000MHZ-B2,"Crystal 16 MHz, 18 pF load",HC-49/US,THT,Top,"Any 16 MHz HC-49/US crystal with an 18 pF load"
2,C6 C7,"Any, C0G / NP0, 50 V","27p: Capacitor 27 pF C0G (crystal load)","Radial, 2.54 mm lead spacing",THT,Top,
5,C4 C5 C8 C9 C11,KEMET C320C104K5R5TA,"100n: Capacitor 100 nF X7R 50 V","Radial, 2.54 mm lead spacing",THT,Top,"C4 = tuner 3.3V (at J7 pin 3), C5 = U1 VDD (pin 20), C8 = MCP2562 VDD, C9 = MCP2562 VIO, C11 = 74HC125 VCC"
3,C1 C2 C3,"Any, X5R, 10 V or more","10u: Capacitor 10 uF ceramic (C1 slot 5 V / U3 in, C2 U3 out, C3 tuner supply)","Radial MLCC, 2.54 mm lead spacing",THT,Top,"Ceramic, not electrolytic: the MCP1700 wants ceramic in and out"
1,C12,"Any, C0G / NP0, 50 V","1n: Capacitor 1 nF C0G (FM coupling to FMI)","Radial, 2.54 mm lead spacing",THT,Top,"C0G only"
1,C13,"Any, X7R, 16 V or more","470n: Capacitor 470 nF (AM coupling to AMI)","Radial MLCC, 2.54 mm lead spacing",THT,Top,
1,C10,"Any, C0G / NP0, 50 V","2.2p: Capacitor 2.2 pF C0G (noise capacitor on the DFS line)","Radial, 2.54 mm lead spacing",THT,Top,"C0G, +-0.25 pF if you can get it"
1,FB1,Murata BL01RN1A2A2B,"Ferrite bead, through-hole (tuner supply)",Axial bead,THT,Top,"Any through-hole bead of about 100 R at 100 MHz, rated 0.1 A or more"
1,L1,"56 nH axial RF inductor","56nH: FM antenna match to RF ground (AN383 fig. 23), Q >= 15 at 100 MHz","Axial, 7.62 mm lead spacing",THT,Top,"Or wind about 5 turns of 0.5 mm enamelled wire on a 3 mm form. Tuned on the bench (README, Tuning L1): fit it in two turned-pin socket contacts so values swap without desoldering. Always fit one: it also drains static off the whip"
2,L1 socket,"2 contacts cut from a turned-pin (machined) SIP socket strip","Sockets for L1, so it can be swapped while tuning",-,THT,Top,"Optional. Any machined-pin strip whose tails fit 0.8 mm holes"
3,R1 R2 R14,"Any 1/4 W 1 % metal film (Yageo MFR-25FBF52-10K or equal)","10k: Resistor (R1 slot ID pull-up, R2 MCLR pull-up, R14 RET buffer off at reset)",Axial DIN0207,THT,Top,
3,R3 R4 R5,"Any 1/4 W 1 % metal film","1k: Resistor (R3 / R4 LEDs, R5 CAN RXD series)",Axial DIN0207,THT,Top,
1,R6,"Any 1/4 W 1 % metal film","604: Resistor (DOUT series)",Axial DIN0207,THT,Top,"600-620 R is fine"
2,R7 R8,"Any 1/4 W 1 % metal film","2k: Resistor (DFS / DCLK series)",Axial DIN0207,THT,Top,
4,R9 R10 R11 R13,"Any 1/4 W 1 % metal film","100k: Resistor (R9 / R10 rail BCK / WS idle pull-downs, R11 tuner reset, R13 RCLK)",Axial DIN0207,THT,Top,
1,R15,"Any 1/4 W 1 % metal film","33: Resistor (RET series, at the rail pin)",Axial DIN0207,THT,Top,
0,R12,"Any 0 R link","0: MCLK to RCLK link (fallback reference clock)",Axial DIN0207,THT,Top,DNP
0,D2,Texas Instruments TPD1E0B04DPYR,"ESD clamp, 1 channel, 0.13 pF (antenna)",X1SON-2 1.0 x 0.6 mm,SMD,Top,"DNP: no through-hole version exists; D4 / D5 and SG1 stand in for it. Pads are on the board if it is ever fab-placed"
2,D4 D5,Vishay 1N5711,"Schottky diode 70 V, 2 pF: antenna ESD clamp pair, back to back to GND (about 0.4 V clamp)",DO-35,THT,Top,"Mounted standing up (2.54 mm pads). Cathode band to the pad marked K. Any 1N5711 (ST, Vishay, onsemi)"
0,SG1,"(PCB copper, nothing to fit)","Spark gap 0.25 mm on the antenna node",-,PCB,Top,"Keep it clean: no solder, flux or conformal coat across the gap"
2,D1 D3,"Any 3 mm green LED","TUNED / STEREO-RDS: status LEDs",3 mm,THT,Top,"Short lead / flat side = cathode = square pad"
1,J1,Sullins PRPC015DBAN-M71RC,"DigiDash slot: pin header 2 x 15, 2.54 mm, right angle",THT,THT,Top,"Same as the other cards. On the bottom edge, pins pointing off the board"
1,J2,Amphenol RF 132289,"SMA jack, edge mount, for 1.6 mm board (antenna)",Edge mount,SMD,Top,"Already on hand. Hand-soldered: centre pin on the top pad, ground legs on both faces. Top edge. For the car whip, a DIN 41585 (Motorola) female to SMA male pigtail"
1,J3,"Any 1 x 6 2.54 mm right-angle male header","ICSP: 1 MCLR, 2 3V3, 3 GND, 4 ICSPDAT, 5 ICSPCLK, 6 NC (PICkit / MPLAB Snap pinout)",THT,THT,Top,"Left edge, pins pointing off the board. Pin 1 (MCLR) is the lowest pin"
1,J4,Sullins PREC003SBAN-M71RC,"Debug serial: pin header 1 x 3, 2.54 mm, right angle (GND, TX, RX)",THT,THT,Top,"Left edge, below J3"
1,J5,Sullins PRPC002SBAN-M71RC,"AM loopstick: pin header 1 x 2, 2.54 mm, right angle (1 AM node, 2 GND)",THT,THT,Top,"Top edge; ferrite loopstick 180-450 uH on a wire pair"
1,J6,Sullins PPTC081LFBN-RC,"Tuner breakout, left header: female header 1 x 8, 2.54 mm, vertical, 8.5 mm",THT,THT,Top,"Any 1 x 8 2.54 mm female header"
1,J7,Sullins PPTC091LFBN-RC,"Tuner breakout, right header: female header 1 x 9, 2.54 mm, vertical, 8.5 mm",THT,THT,Top,"Any 1 x 9 2.54 mm female header"
1,JP1,"Any 1 x 3 2.54 mm straight male header","Tuner address (1 GND, 2 SEN, 3 3V3)",THT,THT,Top,"Fit a shunt on 1-2 (SEN low, I2C address 0x11, the firmware default)"
1,JP1 shunt,Sullins QPC02SXGN-RC,"2.54 mm jumper shunt",-,-,-,"Any 2.54 mm shunt"
1,JP2,"Any 1 x 2 2.54 mm straight male header","AM from whip (1 SMA node, 2 AM node)",THT,THT,Top,"No shunt as delivered (AM from the loopstick only)"

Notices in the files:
README.md:
License:
Two licenses, split by what the file is:
What | License | File
Hardware: every board directory (KiCad schematics, PCBs, footprints, `generate/` output, `fab/`, BOMs), `Housing/` and the mechanical files | CERN Open Hardware Licence v2, Permissive (CERN-OHL-P-2.0) | [`LICENSE-HARDWARE`](LICENSE-HARDWARE)
Software and documentation: `firmware/`, `arduino/`, `tools/`, `scripts/`, the board generator scripts, `docs/` and the READMEs | MIT | [`LICENSE`](LICENSE)
Third-party material keeps its own license: the LVGL fonts in `firmware/esp32_p4_ui/src/fonts/` are ge
